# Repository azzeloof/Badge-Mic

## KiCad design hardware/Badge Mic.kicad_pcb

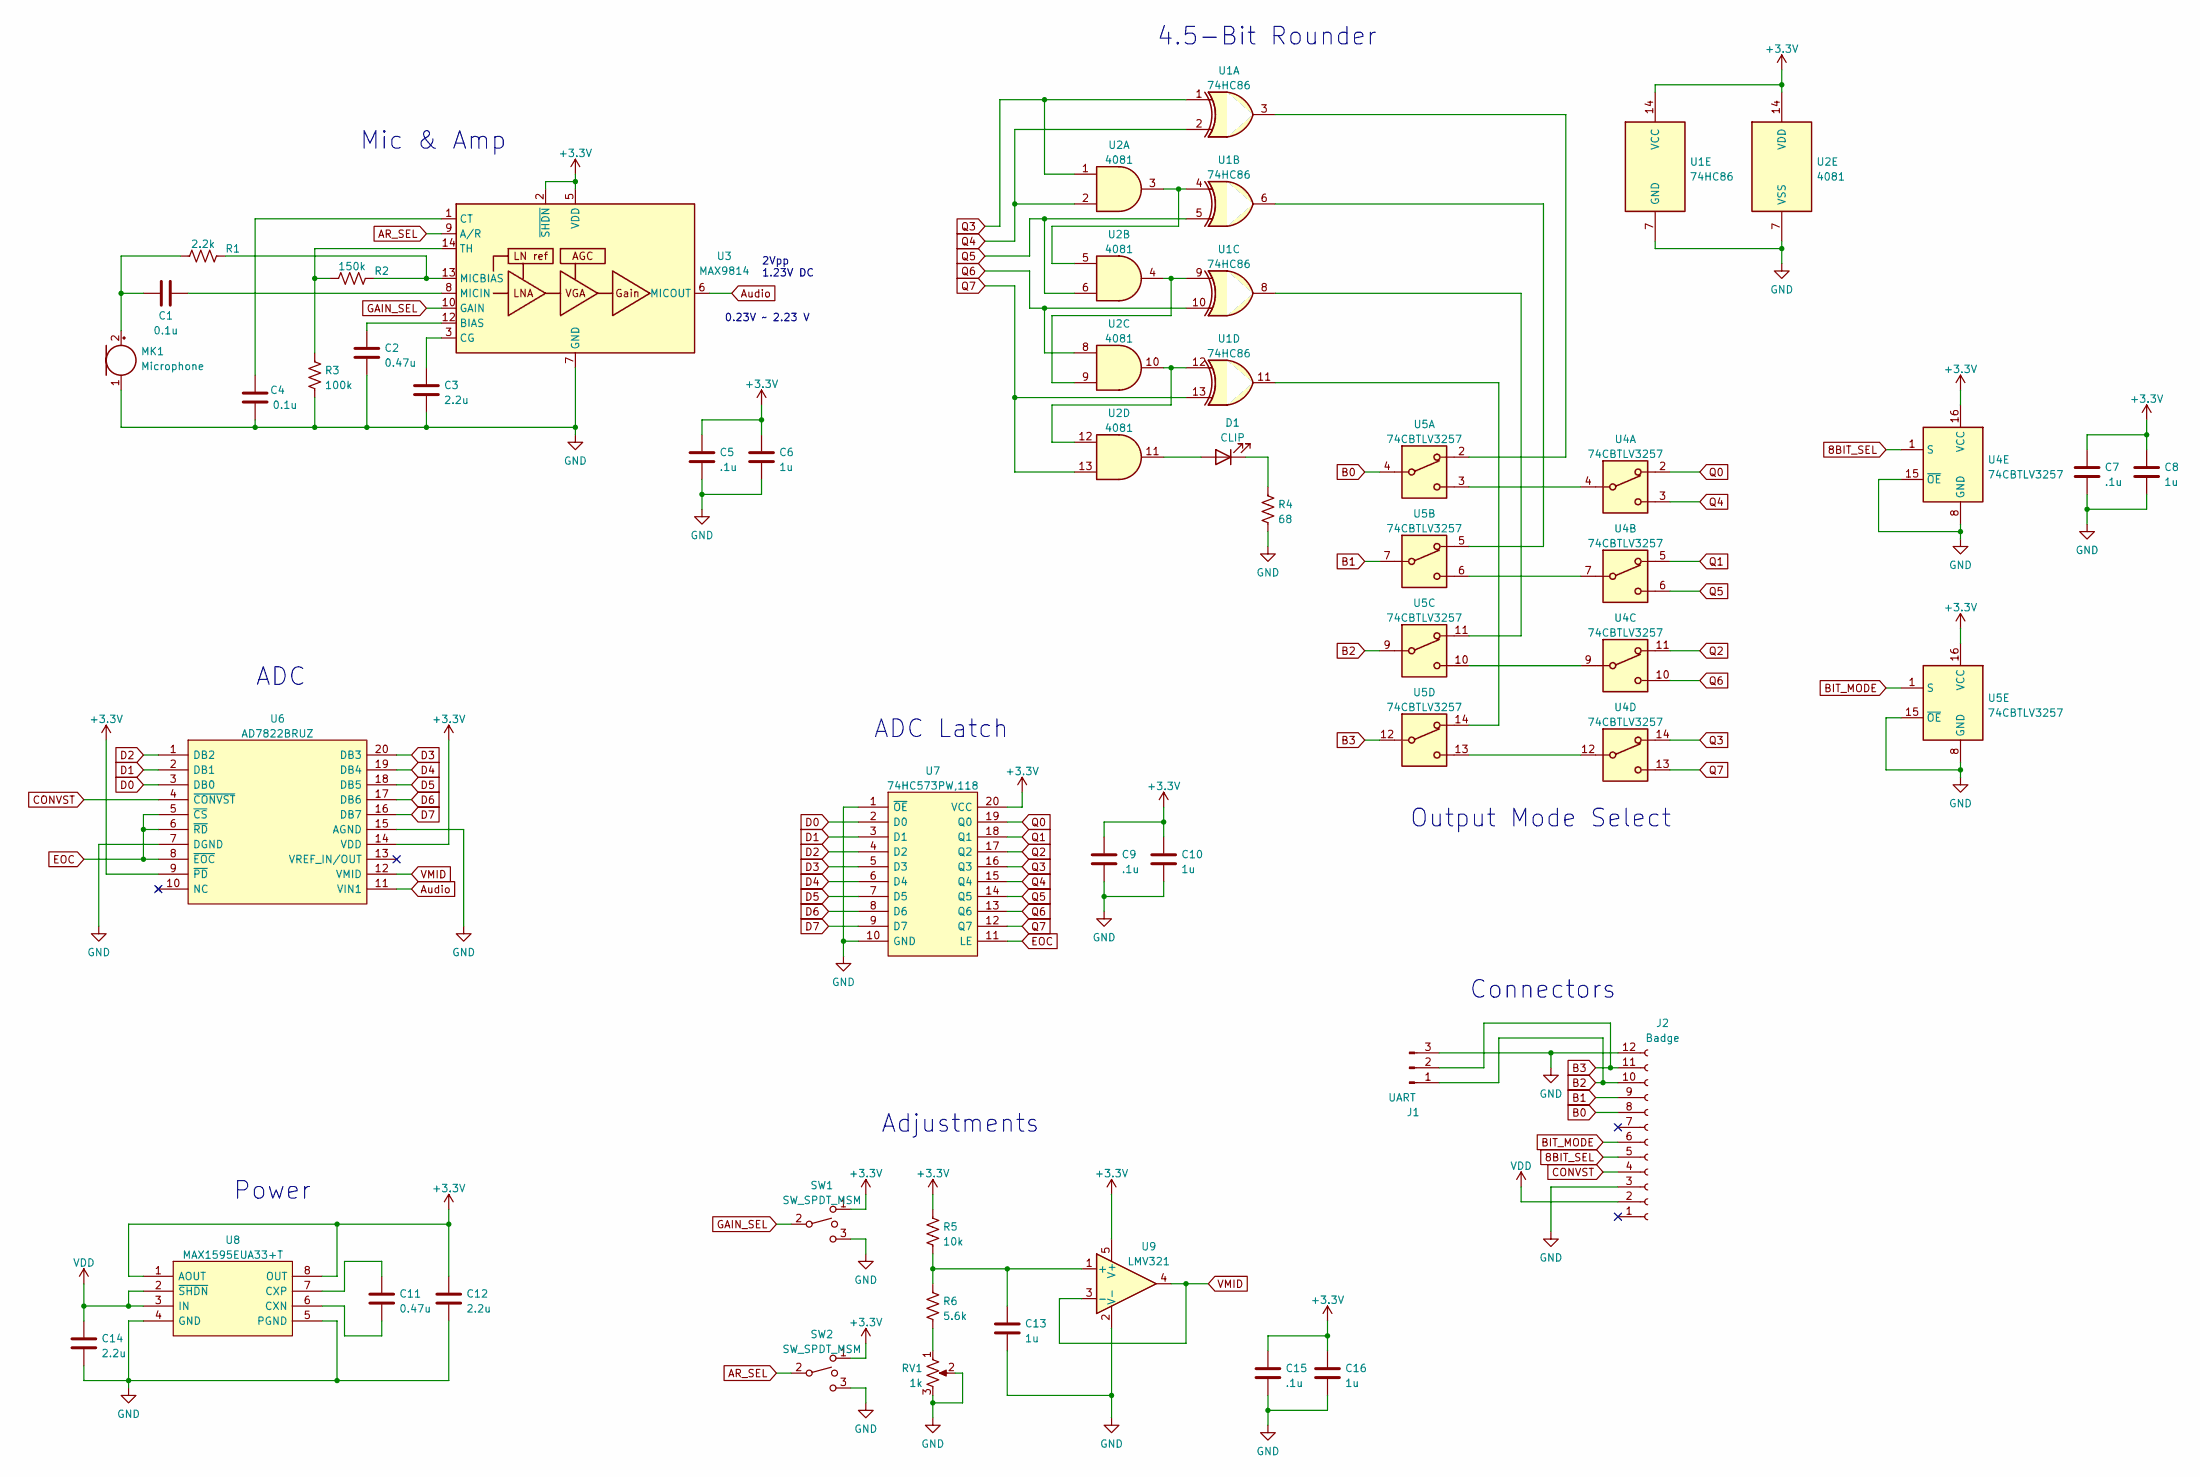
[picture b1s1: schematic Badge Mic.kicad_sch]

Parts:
C1, C4: 0.1u; C_0402_1005Metric_Pad0.74x0.62mm_HandSolder
C2, C11: 0.47u; C_0402_1005Metric_Pad0.74x0.62mm_HandSolder
C3, C12, C14: 2.2u; C_0402_1005Metric_Pad0.74x0.62mm_HandSolder
C5, C7, C9, C15: .1u; C_0402_1005Metric_Pad0.74x0.62mm_HandSolder
C6, C8, C10, C13, C16: 1u; C_0402_1005Metric_Pad0.74x0.62mm_HandSolder
D1: CLIP; LED_0805_2012Metric
J1: UART; PinHeader_1x03_P2.54mm_Horizontal
J2: Badge; PinSocket_1x12_P2.54mm_Horizontal
MK1: Microphone; CMA6542PF
R1: 2.2k; R_0805_2012Metric
R2: 150k; R_0805_2012Metric
R3: 100k; R_0805_2012Metric
R4: 68; R_0805_2012Metric
R5: 10k; R_0805_2012Metric
R6: 5.6k; R_0805_2012Metric
RV1: 1k; Potentiometer_Bourns_3214G_Horizontal
SW1, SW2: SW_SPDT_MSM; SOT175P420X230-3N
U1: 74HC86; SOIC-14_3.9x8.7mm_P1.27mm
U2: 4081; SOIC-14_3.9x8.7mm_P1.27mm
U3: MAX9814; DFN-14-1EP_3x3mm_P0.4mm_EP1.78x2.35mm
U4, U5: 74CBTLV3257; TSSOP-16_4.4x5mm_P0.65mm
U6: AD7822BRUZ; SOP65P640X120-20N; Mouser Part Number 584-AD7822BRUZ
U7: 74HC573PW,118; SOP65P640X110-20N; Mouser Part Number 771-74HC573PW-T
U8: MAX1595EUA33+T; SOP65P490X110-8N; Mouser Part Number 700-MAX1595EUA33T
U9: LMV321; SOT-23-5

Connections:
8BIT_SEL: J2.5, U4.1 (S)
+3V3: C5.1, C6.1, C7.1, C8.1, C9.1, C10.1, C12.1, C15.1, C16.1, R5.1, SW1.1, SW2.1, U1.14 (VCC), U2.14 (VDD), U3.2 (~SHDN), U3.5 (VDD), U4.16 (VCC), U5.16 (VCC), U6.9 (~PD), U6.14 (VDD), U7.20 (VCC), U8.1 (AOUT), U8.8 (OUT), U9.5 (V+)
AR_SEL: SW2.2, U3.9 (A/R)
Audio: U3.6 (MICOUT), U6.11 (VIN1)
B0: J2.8, U5.4
B1: J2.9, U5.7
B2: J1.1, J2.10, U5.9
B3: J1.2, J2.11, U5.12
BIT_MODE: J2.6, U5.1 (S)
CONVST: J2.4, U6.4 (~CONVST)
D0: U6.3 (DB0), U7.2 (D0)
D1: U6.2 (DB1), U7.3 (D1)
D2: U6.1 (DB2), U7.4 (D2)
D3: U6.20 (DB3), U7.5 (D3)
D4: U6.19 (DB4), U7.6 (D4)
D5: U6.18 (DB5), U7.7 (D5)
D6: U6.17 (DB6), U7.8 (D6)
D7: U6.16 (DB7), U7.9 (D7)
EOC: U6.5 (~CS), U6.6 (~RD), U6.8 (~EOC), U7.11 (LE)
GAIN_SEL: SW1.2, U3.10 (GAIN)
GND: C2.2, C3.2, C4.2, C5.2, C6.2, C7.2, C8.2, C9.2, C10.2, C12.2, C13.2, C14.2, C15.2, C16.2, J1.3, J2.3, J2.12, MK1.1 (-), R3.1, R4.2, RV1.2, RV1.3, SW1.3, SW2.3, U1.7 (GND), U2.7 (VSS), U3.4 (GND), U3.7 (GND), U3.11 (GND), U3.15 (GND), U4.8 (GND), U4.15 (~OE), U5.8 (GND), U5.15 (~OE), U6.7 (DGND), U6.15 (AGND), U7.1 (~OE), U7.10 (GND), U8.4 (GND), U8.5 (PGND), U9.2 (V-); also elsewhere on the board
unnamed: C1.1, U3.8 (MICIN)
unnamed 22: C1.2, MK1.2 (+), R1.1; also elsewhere on the board
unnamed: C2.1, U3.12 (BIAS)
unnamed: C3.1, U3.3 (CG)
unnamed: C4.1, U3.1 (CT)
unnamed: C11.1, U8.7 (CXP)
unnamed: C11.2, U8.6 (CXN)
unnamed: C13.1, R5.2, R6.1, U9.1 (+)
unnamed: D1.1 (K), R4.1
unnamed: D1.2 (A), U2.11
unnamed: R1.2, R2.2, U3.13 (MICBIAS)
unnamed: R2.1, R3.2, U3.14 (TH)
unnamed: R6.2, RV1.1
unnamed: U1.3, U5.2
unnamed: U1.4, U2.3, U2.5
unnamed: U1.6, U5.5
unnamed: U1.8, U5.11
unnamed: U1.9, U2.4, U2.9
unnamed: U1.11, U5.14
unnamed: U1.12, U2.10, U2.12
unnamed: U4.4, U5.3
unnamed: U4.7, U5.6
unnamed: U4.9, U5.10
unnamed: U4.12, U5.13
Q0: U4.2, U7.19 (Q0)
Q1: U4.5, U7.18 (Q1)
Q2: U4.11, U7.17 (Q2)
Q3: U1.1, U2.1, U4.14, U7.16 (Q3)
Q4: U1.2, U2.2, U4.3, U7.15 (Q4)
Q5: U1.5, U2.6, U4.6, U7.14 (Q5)
Q6: U1.10, U2.8, U4.10, U7.13 (Q6)
Q7: U1.13, U2.13, U4.13, U7.12 (Q7)
VDD: C14.1, J2.2, U8.2 (~SHDN), U8.3 (IN)
VMID: U6.12 (VMID), U9.3 (-), U9.4

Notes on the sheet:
Power
4.5-Bit Rounder
2Vpp 1.23V DC
ADC Latch
Mic & Amp
Adjustments
Output Mode Select
ADC
Connectors
0.23V ~ 2.23 V

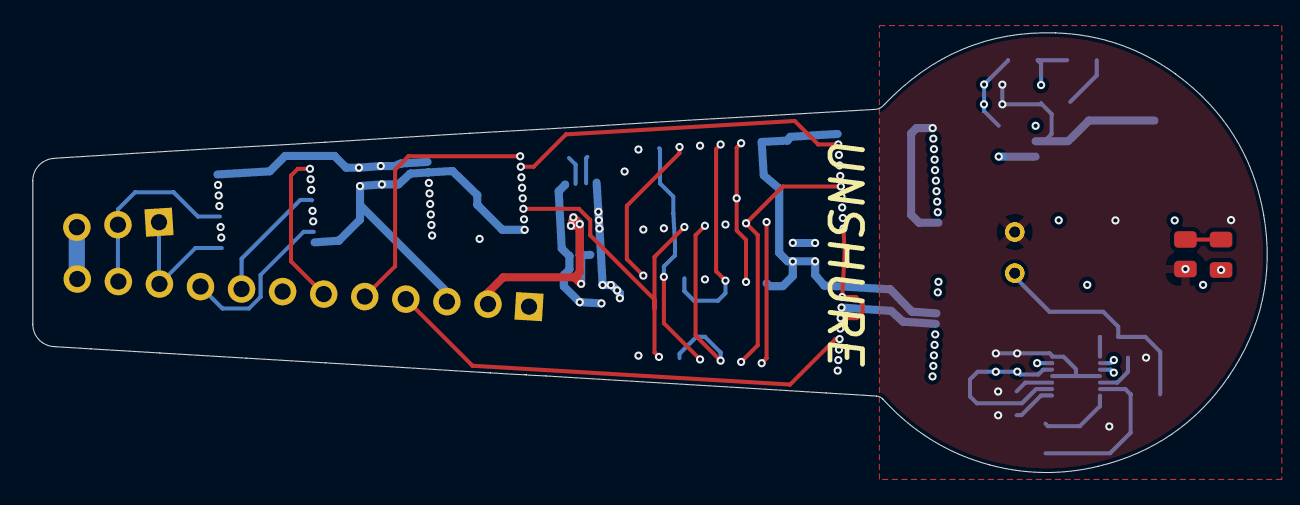
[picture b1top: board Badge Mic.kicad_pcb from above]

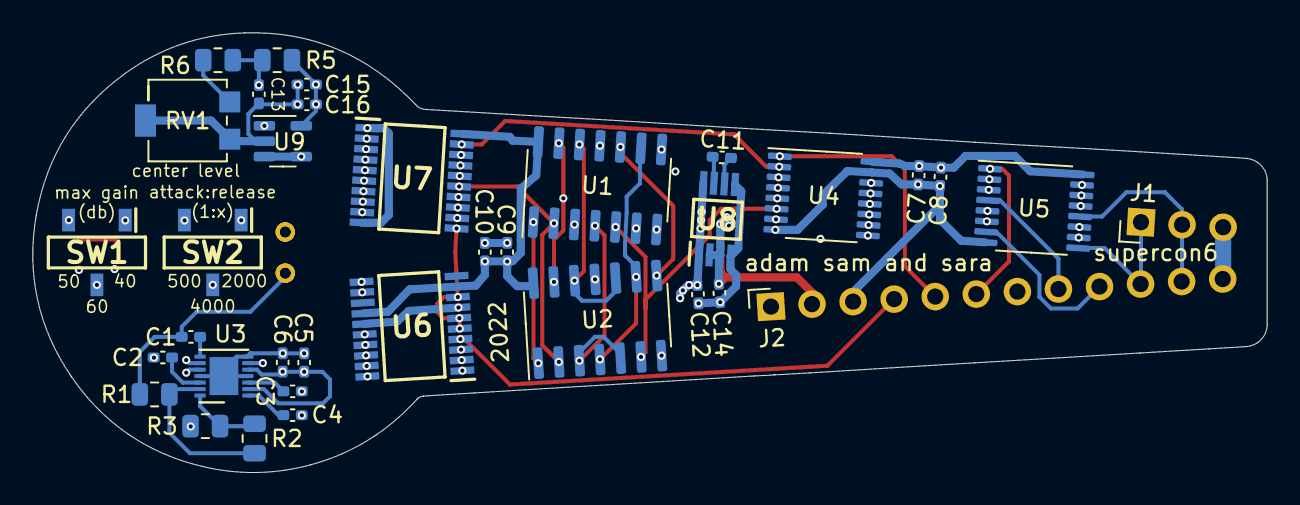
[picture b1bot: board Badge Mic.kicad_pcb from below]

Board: 4 copper layers, 76.2 x 27.1 mm, 39 parts (35 on the bottom side), 55 nets.

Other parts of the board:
MK1#2: Microphone; CMA6542PF

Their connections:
GND: MK1#2.1 (-); also elsewhere on the board
unnamed 22: MK1#2.2 (+); also elsewhere on the board

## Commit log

2022-09-30 Minor layout change
2022-09-30 Fixed DRC errors
2022-10-01 Improved power routing
2022-10-01 Routing improvements and some silkscreen art
